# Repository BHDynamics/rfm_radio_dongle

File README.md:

# DynaLoRa USB Radio Dongle
DynaLoRa USB Radio is a low cost, CircuitPython and Arduino compatible USB radio dongle.

This plaform is equipped with an ATSAMD21 micrcontroller, plus a HopeRF radio module. By default we chose the RFM96W, a LoRa 868 - 915 MHz module based on Semtech's SX1276. You can use an RFM95W for 433 MHz, or an RFM69HCW for generic non-LoRa Sub-GHz radios since they are pin compatible.

Hardware in this repository is licenced under **CERN OHL v1.2**.

## Technical details

- ATSAMD21E18 48 MHz Cortex-M0+ processor with 256 KB flash + 32 KB RAM, compatible with CircuitPython and Arduino
- 32 Mbit SPI flash for storing CircuitPython code and libraries
- High performance HopeRF radio module. You can choose between LoRa (RFM96W, RFM95W) or regular Sub-GHz (RFM69HCW).
- User-controllable WS2812B addressable RGB LED
- Regular user LED
- 3V3 @ 1A power through a DC/DC buck regulator from USB
- MicroSD Card slot
- GPIO header exposing SWD interface, a full SERCOM (enabling external SPI/I2C/UART peripherals) and a DAC for prototyping
- This version comes with an USB-A plug. It should be easy enough to modify the design to offer other options (such as USB-C).

## Documentation

Available in our [Wiki](https://github.com/BHDynamics/rfm_radio_dongle/wiki).

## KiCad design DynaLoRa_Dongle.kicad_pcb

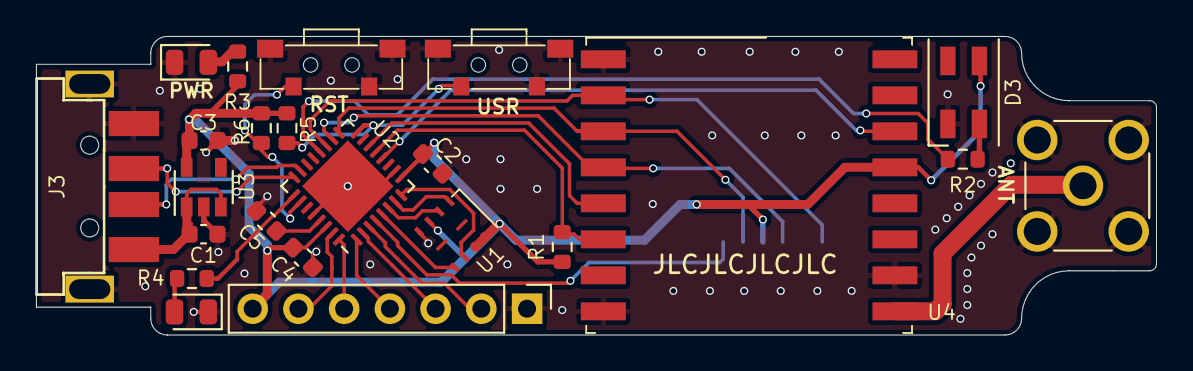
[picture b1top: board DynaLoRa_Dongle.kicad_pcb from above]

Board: 2 copper layers, 62.2 x 16.6 mm, 24 parts (1 on the bottom side), 30 nets.

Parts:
C1, C3: 22uF; C_0603_1608Metric
C2, C4: 100nF; C_0603_1608Metric
C5: 1uF; C_0603_1608Metric
D1, D2: LED_Small; LED_0805_2012Metric
D3: WS2812B; LED_SK6812MINI_PLCC4_3.5x3.5mm_P1.75mm
J1: Conn_01x07; PinHeader_1x07_P2.54mm_Vertical
J2: Conn_Coaxial; SMA_Molex_73251-2200_Horizontal
J3: USB_A; C46394
J4: Micro_SD_Card; TF-102-18
R1, R5, R6: 100k; R_0603_1608Metric
R2, R3, R4: 510R; R_0603_1608Metric
SW1, SW2: SW_Push; 1TS002G-1800-3500-CT
U1: GD25Q32; WSON-8-1EP_3x4mm_P0.8mm
U2: ATSAMD21E18A-AUT; QFN-32-1EP_5x5mm_P0.5mm_EP3.6x3.6mm
U3: ME6211C; SOT-23-5
U4: RFM9X; HOPERF_RFM69HW

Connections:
+3V3: C2.1, C3.1, C4.1, D3.1, J1.7, J4.4, R1.1, R3.1, R5.1, R6.1, U1.3, U1.7, U1.8, U2.9, U2.30, U3.5, U4.13
/FLASH_CS: U1.1, U2.7
/FLASH_SCK: U1.6, U2.8
/FLASH_SDI: U1.2, U2.6
/FLASH_SDO: U1.5, U2.5
/LED: R4.1, U2.25
/PA00: J1.4, U2.1
/PA01: J1.3, U2.2
/PA02: J1.2, U2.3
/RF_CS: U2.14, U4.5
/RF_INT: U2.12, U4.14
/RF_RESET: R1.2, U2.13, U4.6
/RGB: R2.2, U2.20
/SCK: J4.5, U2.18, U4.4
/SDI: J4.7, U2.19, U4.2
/SDO: J4.3, U2.17, U4.3
/SD_CS: J4.2, U2.4
/SWCLK: J1.6, U2.31
/SWDIO: J1.5, U2.32
/USER_BTN: R5.2, SW1.2, U2.16
/nRESET: R6.2, SW2.2, U2.26
GND: C1.2, C2.2, C3.2, C4.2, C5.2, D1.1, D2.1, D3.3, J1.1, J2.2, J3.4, J3.5, J4.6, J4.9, SW1.1, SW1.3, SW1.4, SW2.1, SW2.3, SW2.4, U1.4, U2.10, U2.28, U2.33, U3.2, U4.1, U4.8, U4.10
unnamed: C5.1, U2.29
unnamed: D1.2, R3.2
unnamed: D2.2, R4.2
unnamed: D3.4, R2.1
unnamed: J2.1, U4.9
USB_D+: J3.3, U2.24
USB_D-: J3.2, U2.23
VBUS: C1.1, J3.1, U3.1, U3.3

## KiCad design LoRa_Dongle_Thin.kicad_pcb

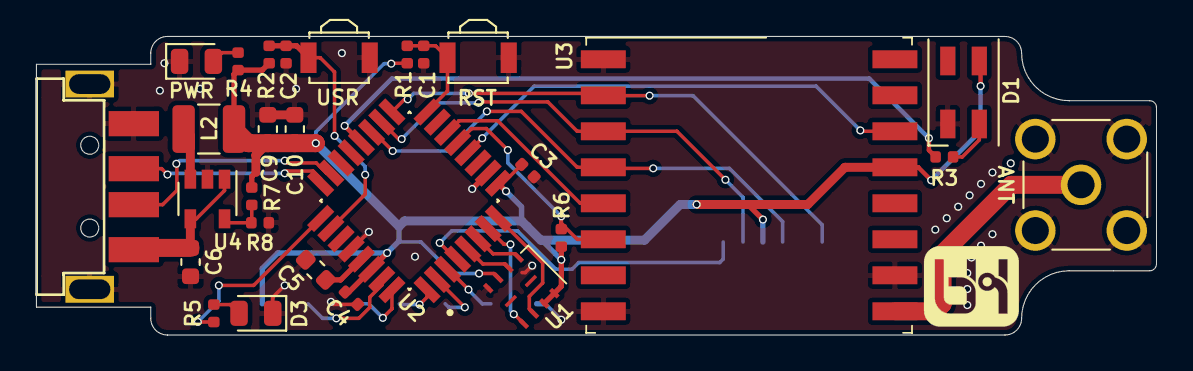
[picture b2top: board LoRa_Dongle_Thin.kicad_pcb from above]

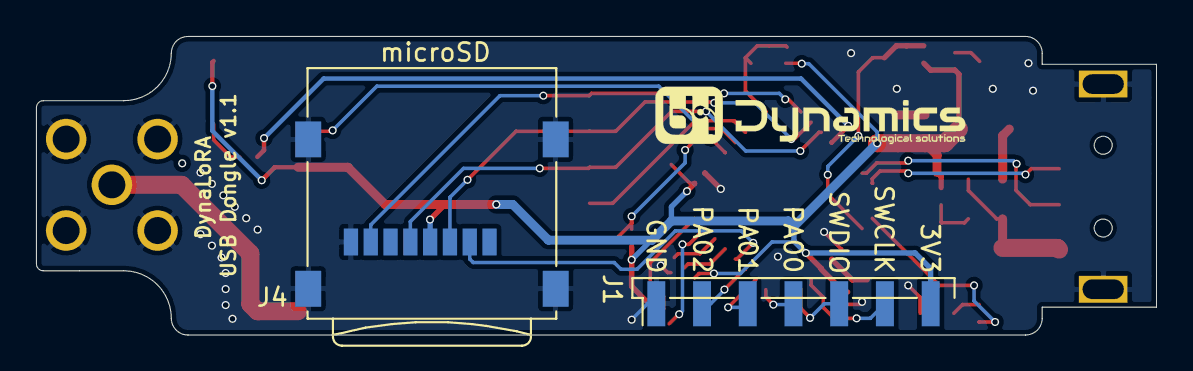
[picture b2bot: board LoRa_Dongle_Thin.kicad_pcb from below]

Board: 2 copper layers, 62.2 x 16.6 mm, 30 parts (2 on the bottom side), 32 nets.

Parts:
C1, C2: 10nF; C_0402_1005Metric
C3, C4: 100nF; C_0402_1005Metric
C5: 1uF; C_0603_1608Metric
C6, C9, C10: 22uF; C_0603_1608Metric
D1: WS2812B; LED_SK6812MINI_PLCC4_3.5x3.5mm_P1.75mm
D2, D3: LED_Small; LED_0805_2012Metric
J1: Conn_01x07; PinHeader_1x07_P2.54mm_Vertical_SMD_Pin1Left
J2: USB_A; C46394
J3: Conn_Coaxial; SMA_Molex_73251-2200_Horizontal
J4: Micro_SD_Card; TF-102-18
L2: 2.2uH; L_1210_3225Metric
R1, R2, R6, R7: 100k; R_0402_1005Metric
R3, R4, R5: 510R; R_0402_1005Metric
R8: 22k; R_0402_1005Metric
SW1, SW2: SW_Push; SW_SPST_B3U-3000P
U1: GD25Q32; WSON-8-1EP_3x4mm_P0.8mm
U2: ATSAMD21E18A-AUT; QFP80P900X900X120-32N
U3: RFM9X; HOPERF_RFM69HW
U4: SY80XX; SOT-23-5

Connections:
+3V3: C3.1, C4.1, C9.1, C10.1, D1.1, J1.7, J4.4, L2.2, R1.1, R2.1, R4.1, R6.1, R7.1, U1.3, U1.7, U1.8, U2.9, U2.30, U3.13
/FLASH_CS: U1.1, U2.6
/FLASH_SCK: U1.6, U2.8
/FLASH_SDI: U1.2, U2.5
/FLASH_SDO: U1.5, U2.7
/LED: R5.1, U2.25
/PA00: J1.4, U2.1
/PA01: J1.3, U2.2
/PA02: J1.2, U2.3
/RF_CS: U2.14, U3.5
/RF_INT: U2.12, U3.14
/RF_RESET: R6.2, U2.13, U3.6
/RGB: R3.2, U2.20
/SCK: J4.5, U2.19, U3.4
/SDI: J4.7, U2.17, U3.2
/SDO: J4.3, U2.18, U3.3
/SD_CS: J4.2, U2.4
/SWCLK: J1.6, U2.31
/SWDIO: J1.5, U2.32
/USER_BTN: C1.1, R1.2, SW1.1, U2.16
/nRESET: C2.1, R2.2, SW2.1, U2.26
GND: C1.2, C2.2, C3.2, C4.2, C5.2, C6.2, C9.2, C10.2, D1.3, D2.1, D3.1, J1.1, J2.4, J2.5, J3.2, J4.8, J4.9, R8.2, SW1.2, SW2.2, U1.4, U2.10, U2.28, U3.1, U3.8, U3.10, U4.2
unnamed: C5.1, U2.29
unnamed: D1.4, R3.1
unnamed: D2.2, R4.2
unnamed: D3.2, R5.2
unnamed: J3.1, U3.9
unnamed: L2.1, U4.3
unnamed: R7.2, R8.1, U4.5
USB_D+: J2.3, U2.24
USB_D-: J2.2, U2.23
VBUS: C6.1, J2.1, U4.1, U4.4

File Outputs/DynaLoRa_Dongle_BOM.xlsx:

| Reference(s) | Qty | Part Number | Value | Comments
 | C1, C2 | 2 |  | 10nF | 10 nF 0402
 | C3, C4 | 2 |  | 100nF | 100 nF 0402
 | C5 | 1 |  | 1uF | 1 uF 0603
 | C6, C9, C10 | 3 |  | 22uF | 22 uF 0603 X5R or X7R
 | D1 | 1 | WS2812B-MINI | WS2812B-MINI | Addressable LED RGB
 | D2 | 1 |  | LED_Small | 0805 Red LED
 | D3 | 1 |  | LED_Small | 0805 Blue LED
 | J1 | 1 | DO NOT PLACE | Conn_01x07 | Pin header 1x07 2.54 mm SMD horizontal
 | J2 | 1 | U217-041N-4BV81 | USB_A | USB-A 2.0 Plug
 | J3 | 1 | PCB.RPSMAFRA.HT* | Conn_Coaxial | SMA THT female connector with pin.
 | J4 | 1 | TF-102-18 | Micro_SD_Card | MicroSD card slot
 | L2 | 1 | L1210R2R2MDWIT | 2.2uH | 1210 2.2uH 2A Inductor
 | R1, R2, R6, R7 | 4 |  | 100k | 100k 0402 1%
 | R3, R4, R5 | 3 |  | 510R | 510 ohm 0402 1%
 | R8 | 1 |  | 22k | 22.1k 0402 1%
 | SW1, SW2 | 2 | B3U-3000P | SW_Push | SMD push button
 | U1 | 1 | GD25Q32CNIGR | GD25Q32 | 32 Mbit QSPI flash memory
 | U2 | 1 | ATSAMD21E18A-AUT | ATSAMD21E18A | Cortex-M0 MCU
 | U3 | 1 | RFM95W | RFM9X | 868-915 MHz LoRa Radio module
 | U4 | 1 | SY8088AAC | SY8088 | DC/DC Buck converter

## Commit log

2020-11-25 Initial commit, empty project
2020-11-25 Schematics WIP, SPI missing
2020-12-01 v1.1 - Add GPIO header + SD Card
2020-12-01 Add LICENSE.md
2020-12-10 Version 1.1 - Thin
2021-02-04 v1.2, fix SD card GND and button silkscreen. RC
2021-02-10 Update outputs folder
2021-02-26 v3 changes
    - Use standard 2.54 mm vertical THT pin header! (finally)
    - Replace buttons for bigger ones that are easier to press (the same ones as DynOSSAT-EDU)
    - Replace DC/DC for a 500 mA LDO to simplify assembly, since USB won't source more than 500 mA anyway
    - The ATSAMD21E18 is now the QFN version instead of QFP
    - Replace pin naming on the header by their Arduino/CircuitPython naming (i.e. PA00 is now D0, etc)
    It should be fully compatible with the v2, no software changes needed.
